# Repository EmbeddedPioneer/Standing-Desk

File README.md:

# Standing Desk 

## Overview  
The **Standing Desk** is an electrically adjustable desk designed for ergonomic comfort, allowing users to transition between sitting and standing positions with ease. The desk features a motorized lifting mechanism controlled by a custom PCB and firmware.  

This repository contains all the necessary files to build and assemble the desk, including mechanical parts, electronic schematics, PCB design, and firmware.  

## Features  
- **Electric Height Adjustment** – Smooth motorized movement for seamless transitions between sitting and standing positions.  
- **Memory Presets** – Store preferred height positions for quick adjustments.
- **Button Control** – User-friendly interface for height adjustment.
- **Supports up to 20kg Load** – Sturdy design capable of handling up to **20kg** of weight.  
---

## Key Components List  
### 🔩 Mechanical Components  
- **MDF Laser-Cut Parts** – Custom-designed structural parts for the desk frame.  
- **Metal Profiles** – design is open for modefications and does not affect the operation.  
- **Lead Screws & Guide Rails** – Ensures precise height adjustment.  
- **Motor Brackets & Couplings** – Secure motor attachment and efficient power transfer.  

### ⚡ Electrical Components  
- **High Torque DC Motor with Gearbox** – Powers the height adjustment mechanism.  
- **Custom PCB** – Controls motor movements and user interactions.  
- **Motor Driver L298N** – Regulates power delivery to motors.  
- **Power Supply  (24V 5A or based on motor requirements)** – Provides sufficient power for motors and electronics.  
- **Optical Endstop & normal Endstop** – Detects desk height limits for safety.  
- **Microcontroller (ATmega328P)** – Handles desk automation and user input.  
- **Buttons** – User interface for manual adjustments.  
---

## Hardware Overview  
1. **Inputs**:  
   - **Power Supply**: 12V or 24V (Depends on DC motor model) and GND.  
   - **Control Switches**:  
     - 2 Switches for UP and DOWN.  
     - 1 Switch for Homing To the Min Position .
     - 1 Switch to save the current position. 
     - 1 Switch to select the Mode (Saved Position).
     - 1 Endstop to detects the Min Position when Homing.
     - 1 Optical Endstop to calculate the travel from the Min position to the current position.
2. **Outputs**:  
   - 1 High torque DC motor.
3. **PCB Design**:  
   - Single-layer for easy DIY manufacturing.  
   - THT components for straightforward soldering.  
   - Compact layout with labeled connections.  

---

## Firmware  
The firmware is written on the **Arduino platform** and requires the ATmega328P chip to be bootloaded.  
### Setup:  
1. Burn the **Arduino bootloader** onto the ATmega328P chip.  
2. Open the provided Arduino code in the repository.  
3. Compile and upload the code to the ATmega328P using an **Arduino-compatible programmer**.  

---

## Operation  

### Powering On  
1. Connect the **24V/12V power supply** to the PCB.  
2. Ensure all connections (motors, endstops, buttons) are properly secured.  

### Manual Height Adjustment  
- Use the **UP** and **DOWN** buttons to control the desk height.  
- The **motorized mechanism** moves the desk smoothly between sitting and standing positions.  
- The **optical endstop** continuously tracks position changes to ensure precise height adjustments.  

### Homing Process  
- When first powered on, the system requires **homing** to calibrate its position.  
- Press the **Homing button**, and the desk will move to the **minimum position**.  
- The **mechanical endstop** will detect the lower limit and stop movement.  
- Once homing is complete, the system is ready for normal operation.  

### Memory Presets (Saved Position)  
- The desk allows storing one specific height positions for quick recall.  
- Press the **Mode button** to switch to **Saved Position Mode**.  
- Adjust the desk to a preferred height and **save it** using save button.  
- When  pressing **MODE** the disk will move to the stored positions.  

### Safety Features  
- **Limit Switches:** Prevents movement beyond mechanical constraints.  

### Shutdown Procedure  
- Lower the desk to the minimum position (recommended).  
- Disconnect the **power supply** if the desk won’t be used for an extended period.  

---

## Repository Structure  
- **Hardware:** PCB design files, schematics, KiCad Files, and BOM
- **Firmware:** Arduino firmware and bootloader setup
- **Documentation:** User guides, truth table, and setup instructions
- **Real-Tests:** Images, videos, and reports of real-world tests

---

## Feature Improvements  
- **Stronger Frame & Higher Load Capacity** – Reinforce the structure to support heavier loads beyond 20kg.  
- **Dual-Motor System** – Enhance stability and lifting efficiency with synchronized motors.  
- **LCD Display** – Display real-time height, system status, and saved presets.  
- **Soft Start & Stop Motion** – Implement acceleration control for smoother transitions.  

---

## License  
This project is released under the **MIT License**.  

Feel free to contribute, modify, and enhance this project.

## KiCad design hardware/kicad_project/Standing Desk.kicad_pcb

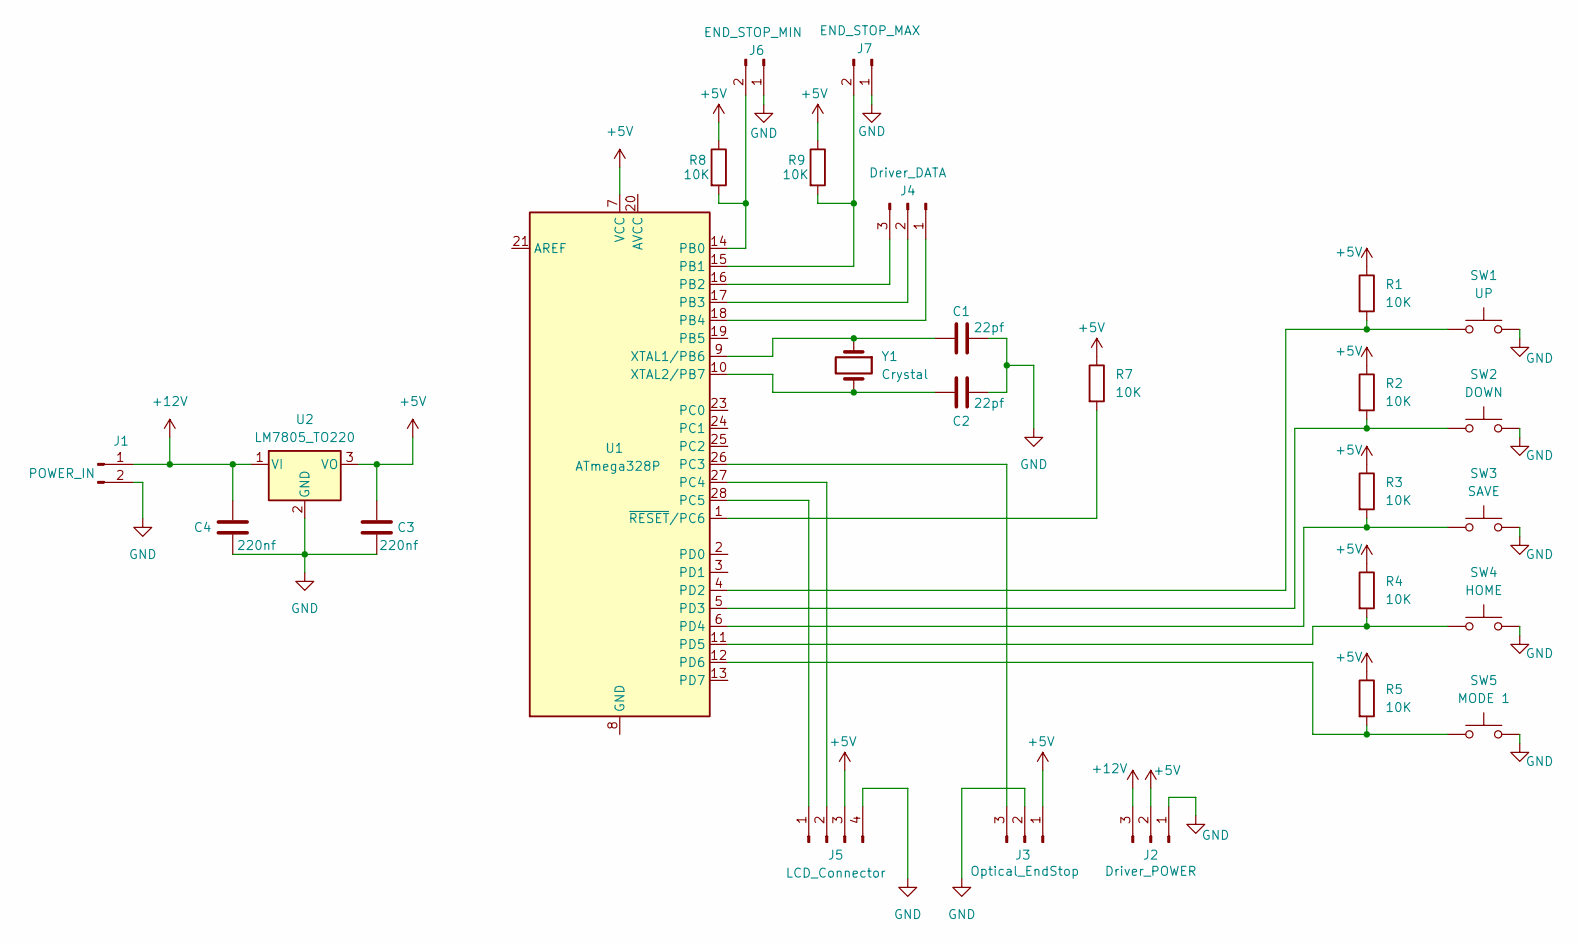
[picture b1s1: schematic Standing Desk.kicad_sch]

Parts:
C1, C2: 22pf; C_Disc_D6.0mm_W4.4mm_P5.00mm
C3, C4: 220nf; C_Disc_D7.5mm_W4.4mm_P5.00mm
J1: POWER_IN; PinHeader_1x02_P2.54mm_Vertical
J2: Driver_POWER; PinHeader_1x03_P2.54mm_Vertical
J3: Optical_EndStop; PinHeader_1x03_P2.54mm_Vertical
J4: Driver_DATA; PinHeader_1x03_P2.54mm_Vertical
J5: LCD_Connector; PinHeader_1x04_P2.54mm_Vertical
J6: END_STOP_MIN; PinHeader_1x02_P2.54mm_Vertical
J7: END_STOP_MAX; PinHeader_1x02_P2.54mm_Vertical
R1, R2, R3, R4, R5, R7, R8, R9: 10K; R_Axial_DIN0207_L6.3mm_D2.5mm_P10.16mm_Horizontal
SW1: UP; SW_SPST_Omron_B3F-40xx
SW2: DOWN; SW_SPST_Omron_B3F-40xx
SW3: SAVE; SW_SPST_Omron_B3F-40xx
SW4: HOME; SW_SPST_Omron_B3F-40xx
SW5: MODE 1; SW_SPST_Omron_B3F-40xx
U1: ATmega328P; DIP-28_W7.62mm
U2: LM7805_TO220; TO-220-3_Vertical
Y1: Crystal; Crystal_HC52-U_Vertical

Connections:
+5V: C3.1, J2.2, J3.1, J5.3, R1.1, R2.1, R3.1, R4.1, R5.1, R7.1, R8.1, R9.1, U1.7 (VCC), U2.3 (VO); also elsewhere on the board
+12V: C4.1, J1.1, J2.3, U2.1 (VI)
GND: C1.2, C2.2, C3.2, C4.2, J1.2, J2.1, J3.2, J5.4, J6.1, J7.1, SW1.2, SW2.2, SW3.2, SW4.2, SW5.2, U2.2 (GND); also elsewhere on the board
unnamed: J3.3, U1.26 (PC3)
unnamed: J4.1, U1.18 (PB4)
unnamed: J4.2, U1.17 (PB3)
unnamed: J4.3, U1.16 (PB2)
unnamed: J5.1, U1.28 (PC5)
unnamed: J5.2, U1.27 (PC4)
unnamed: J6.2, R8.2, U1.14 (PB0)
unnamed: J7.2, R9.2, U1.15 (PB1)
unnamed: U1.8 (GND), U1.22 (GND)
unnamed: R1.2, SW1.1, U1.4 (PD2)
unnamed: R2.2, SW2.1, U1.5 (PD3)
unnamed: R3.2, SW3.1, U1.6 (PD4)
unnamed: R4.2, SW4.1, U1.11 (PD5)
unnamed: R5.2, SW5.1, U1.12 (PD6)
unnamed 17: U1.13 (PD7); also elsewhere on the board
unnamed: C1.1, U1.9 (XTAL1/PB6), Y1.1
unnamed: C2.1, U1.10 (XTAL2/PB7), Y1.2
unnamed: R7.2, U1.1 (~RESET/PC6)

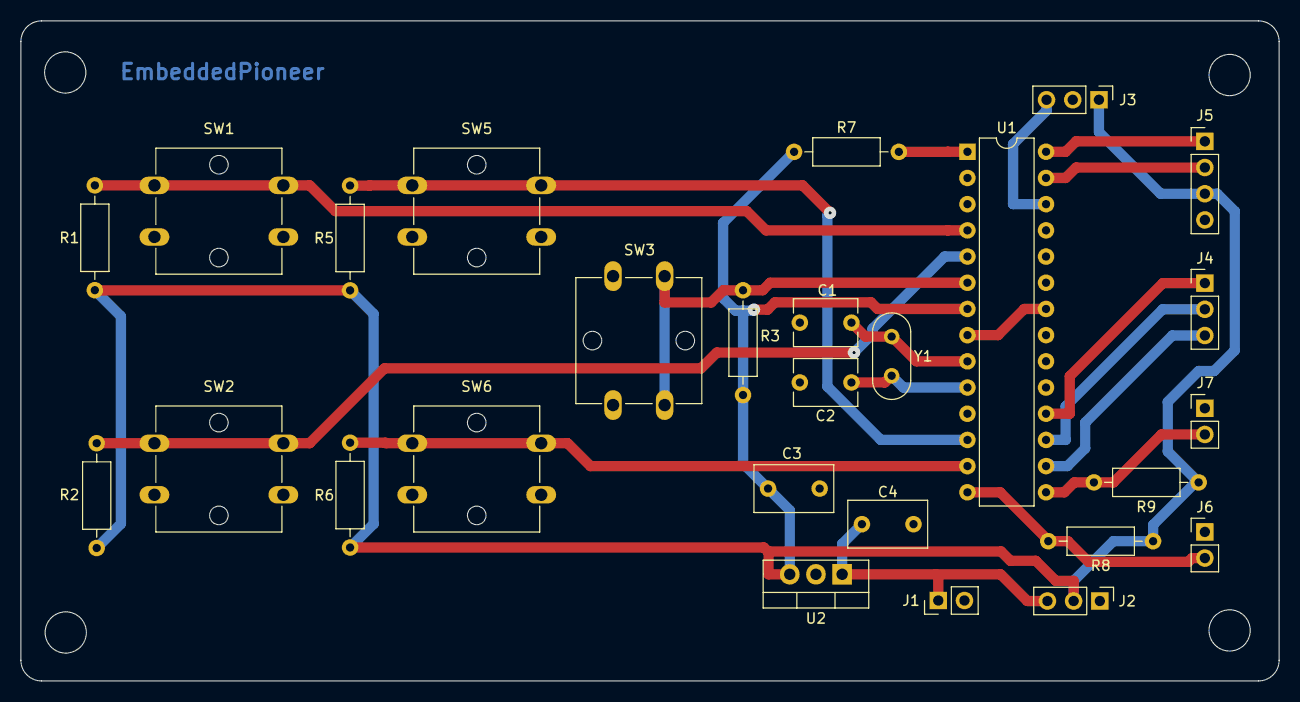
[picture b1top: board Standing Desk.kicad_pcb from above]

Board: 2 copper layers, 122.0 x 64.0 mm, 27 parts (0 on the bottom side), 20 nets.

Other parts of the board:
R6: 10K; R_Axial_DIN0207_L6.3mm_D2.5mm_P10.16mm_Horizontal
SW6: Home; SW_SPST_Omron_B3F-40xx

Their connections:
+5V: R6.1; also elsewhere on the board
GND: SW6.2; also elsewhere on the board
unnamed 17: R6.2, SW6.1; also elsewhere on the board

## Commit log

2025-02-11 Create
2025-02-11 Create m
2025-03-28 Create temp
2025-03-29 Create bom
